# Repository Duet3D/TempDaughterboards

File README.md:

# TempDaughterboards

The Design files for [PT100](https://www.duet3d.com/PT100_DaughterBoard) and [Thermocouple](https://www.duet3d.com/TC_K_DaughterBoard) daughterboards for Duet boards

Current version 1.1, archive containes older versions

The designs are licensed under the CERN OHL v1.2

Documentation:
https://docs.duet3d.com/Duet3D_hardware/Accessories/Thermocouple_Daughterboard
https://docs.duet3d.com/en/Duet3D_hardware/Accessories/PT100_Temperature_Daughterboard

## Support requests

Please use the [forum](https://forum.duet3d.com) for support requests.

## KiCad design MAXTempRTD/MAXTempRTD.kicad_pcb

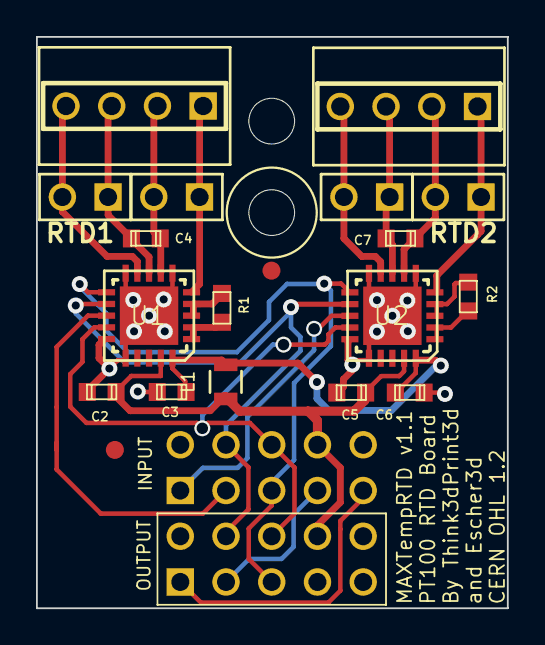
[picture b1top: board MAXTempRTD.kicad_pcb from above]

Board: 2 copper layers, 26.2 x 31.7 mm, 19 parts (1 on the bottom side), 22 nets.

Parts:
C2, C3, C5, C6: 0.1u; C_0603
C4, C7: 100nF; C_0603
J1, J2, J3, J4: J; JUMPER
L1: 100 µH; R_0805
P1: RTD1; SCREW_TERMINAL_4x1
P2: RTD2; SCREW_TERMINAL_4x1
P3: OUTPUT; MAX_TEMP_DB
P4: INPUT; MAX_TEMP_DB_inv
R1, R2: 400R 0.1% 25ppm/C; R_0603
U1, U2: MAX31865; QFN20_5x5

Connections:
3.3V: C2.1, C5.1, L1.1, P3.8, P4.8, U1.19, U2.19
A_3.3V: C3.1, C6.1, L1.2, U1.20, U2.20
CS_1: P4.3, U1.13
CS_2: P4.1, U2.13
CS_3: P3.3, P4.7
CS_4: P3.1, P4.9
GND: C2.2, C3.2, C5.2, C6.2, P3.2, P4.2, U1.6, U1.10, U1.15, U1.16, U1.21, U2.6, U2.10, U2.15, U2.16, U2.21
MISO: P3.6, P4.6, U1.14, U2.14
MOSI: P3.5, P4.5, U1.11, U2.11
unnamed: R1.1, U1.1, U1.2
unnamed: R1.2, U1.3, U1.4
unnamed: R2.1, U2.1, U2.2
unnamed: R2.2, U2.3, U2.4
RC_1_A1: J1.1, P1.1, U1.5
RC_1_A2: C4.1, J1.2, P1.2, U1.7
RC_1_B1: C4.2, J2.1, P1.3, U1.8
RC_1_B2: J2.2, P1.4, U1.9
RC_2_A1: J3.1, P2.1, U2.5
RC_2_A2: C7.1, J3.2, P2.2, U2.7
RC_2_B1: C7.2, J4.1, P2.3, U2.8
RC_2_B2: J4.2, P2.4, U2.9
SCLK: P3.4, P4.4, U1.12, U2.12

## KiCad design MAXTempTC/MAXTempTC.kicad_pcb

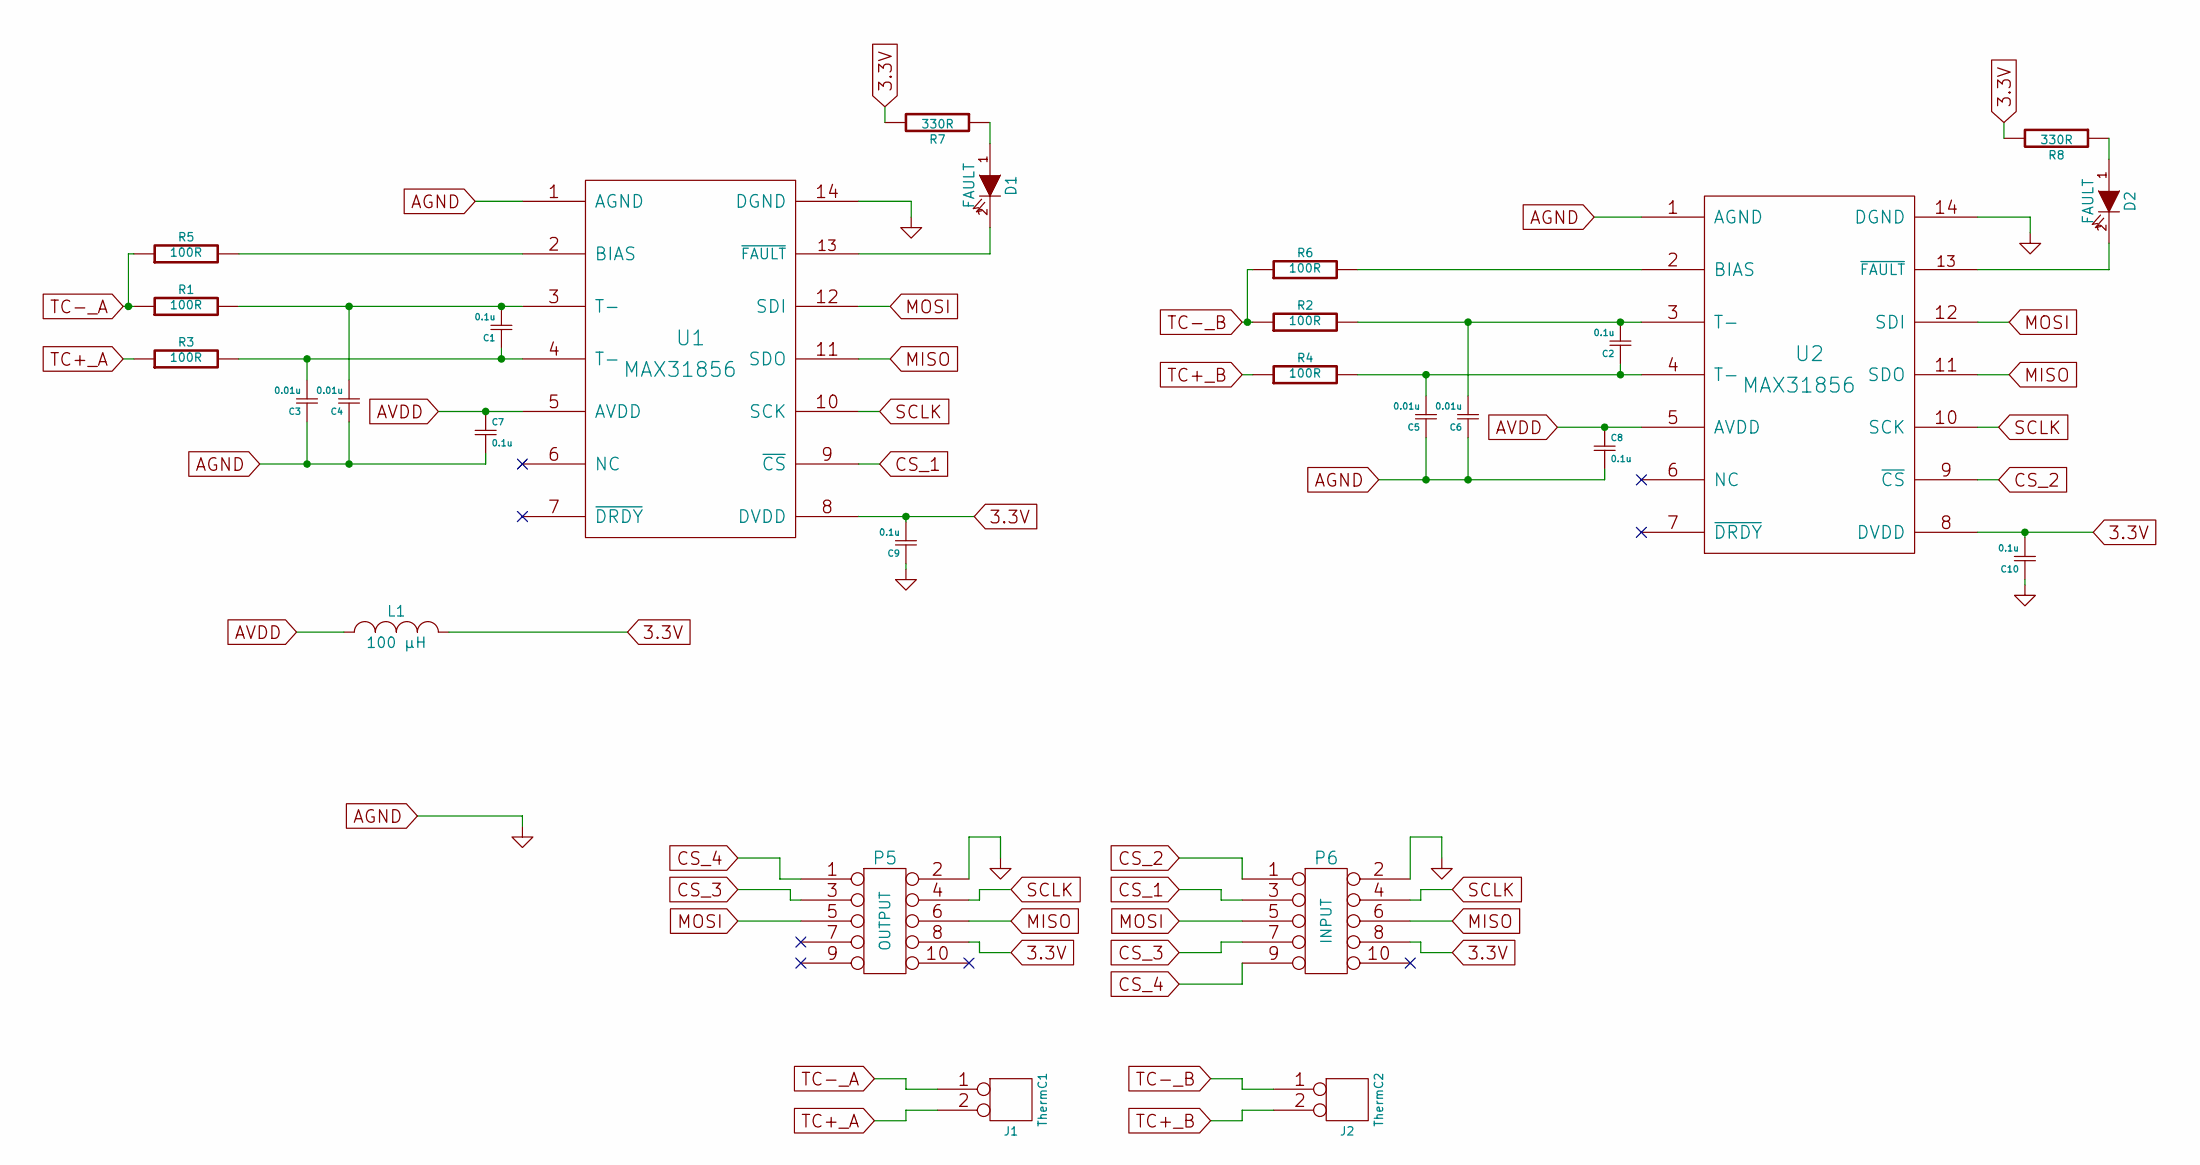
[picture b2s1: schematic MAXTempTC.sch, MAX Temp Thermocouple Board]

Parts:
C1, C2, C7, C8, C9, C10: 0.1u; C_0603
C3, C4, C5, C6: 0.01u; C_0603
D1, D2: FAULT; D_0603
J1: ThermC1; PIN_ARRAY_2X1
J2: ThermC2; PIN_ARRAY_2X1
L1: 100 µH; R_0805
P5: OUTPUT; MAX_TEMP_DB
P6: INPUT; MAX_TEMP_DB_inv
R1, R2, R3, R4, R5, R6: 100R; R_0603
R7, R8: 330R; R_0603
U1, U2: MAX31856; TSSOP-14

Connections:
3.3V: C9.2, C10.2, L1.2, P5.8, P6.8, R7.2, R8.2, U1.8 (DVDD), U2.8 (DVDD)
AGND: C3.1, C4.1, C5.1, C6.1, C7.2, C8.2, C9.1, C10.1, P5.2, P6.2, U1.1 (AGND), U1.14 (DGND), U2.1 (AGND), U2.14 (DGND)
AVDD: C7.1, C8.1, L1.1, U1.5 (AVDD), U2.5 (AVDD)
CS_1: P6.3, U1.9 (~CS)
CS_2: P6.1, U2.9 (~CS)
CS_3: P5.3, P6.7
CS_4: P5.1, P6.9
MISO: P5.6, P6.6, U1.11 (SDO), U2.11 (SDO)
MOSI: P5.5, P6.5, U1.12 (SDI), U2.12 (SDI)
unnamed: C1.1, C3.2, R3.2, U1.4 (T-)
unnamed: C1.2, C4.2, R1.2, U1.3 (T-)
unnamed: C2.1, C5.2, R4.2, U2.4 (T-)
unnamed: C2.2, C6.2, R2.2, U2.3 (T-)
unnamed: D1.1 (A), R7.1
unnamed: D1.2 (K), U1.13 (~FAULT)
unnamed: D2.1 (A), R8.1
unnamed: D2.2 (K), U2.13 (~FAULT)
unnamed: R5.2, U1.2 (BIAS)
unnamed: R6.2, U2.2 (BIAS)
SCLK: P5.4, P6.4, U1.10 (SCK), U2.10 (SCK)
TC+_A: J1.2 (PM), R3.1
TC+_B: J2.2 (PM), R4.1
TC-_A: J1.1, R1.1, R5.1
TC-_B: J2.1, R2.1, R6.1

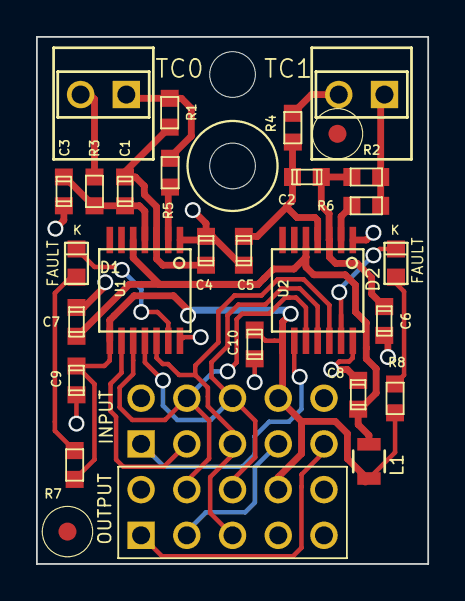
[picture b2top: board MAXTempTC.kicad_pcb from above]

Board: 2 copper layers, 21.7 x 29.3 mm, 29 parts (1 on the bottom side), 24 nets.

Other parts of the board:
M3, M3#2: FID; Fiducial_1mm_Dia_2.54mm_Outer_CopperTop

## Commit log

2017-04-01 :circus_tent: Added .gitattributes & .gitignore files
2017-04-01 PT100 and Thermocouple Daughterboards
    Compatible with DuetWifi and DuetEthernet
2017-04-01 created readme.md
2018-08-29 Updated v1.1 source files
2022-06-28 added Step file for TC DB
2022-06-28 Added Step file for PT100 DB
2026-06-17 Replaced x0rtrunks with droftarts

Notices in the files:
MAXTempRTD/MAXTempRTD.kicad_pcb:
CERN OHL 1.2
